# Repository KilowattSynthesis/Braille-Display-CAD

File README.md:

# Braille-Display-CAD

Experimental design for a braille display using build123d CAD in Python

## Interesting Parts

* 4mm x 8mm DC Motors: https://www.aliexpress.com/item/1005004370822475.html
* 2.8mm x 3.9mm DC Motors: https://www.aliexpress.com/item/1005006897190118.html

## Explored Ideas

### Pogo Spools

* Laser printer fuser-like roller mask.
    * Branch: `archive/pogo-spools`
    * Files: `ideas_pogo_spool_mask/`
* Made PCB with small stepper motors, tiny CAD parts (spools).

### RF Inductors as Electromagnets

* Use Mouser's "RF Inductors" selection, mounting an inductor vertically.
    * Branches: `archive/inductor-smd-vertical`, `archive/inductor-smd-flat`
    * Eaton makes good-looking ones. 3225 metric (1210 imp) is too big; 2520 metric (1008 imp) might be okay. 2012 metric (0805 imp) is great!
    * "Power Inductors - Leaded" are never small enough.
    * Filter to >= 20uH inductance. Filter to >=70 mA.
    * Examples (Vertical-Mount):
        * BWLD00241715 -> Not stocked in smaller quantities, though.
            * 2.4 mm x 1.72 mm x 1.52 mm
        * LBR2012T470M -> 0805 imp (2012 metric). 47uH. 75mA rated max.
    * Examples (Horizontal-Mount):
        * VLS201612CX-220M-1 -> 22uF, very good, but shielded.

* Test results:
    * 4mm x 4mm x 3mm 33uH coil-wound SMD power inductor (ASPI-4030S-330M-T) can point a magnet. Magnets stick to the inductor always though.
    * Several inductors, up to 6mm diameter (and 1-2 MH), with 24V get very hot, but don't levitate a 1mm or 2mm neodymium magnet.
        * Good at pointing pointing the magnet, if it starts far away.
        * Cannot remove the magnet from the inductor once it's stuck.

* **Conclusion**: RF inductors don't have enough magnetic force to levitate 1mm or 2mm neodymium magnets.

### Nut/Bolt Grid

* Turn a bolt in a threaded hole/nut. Each bolt is a dot. User directly touches the dot.
* Movement can be done with one motor per dot (very tiny motors, maybe stacked), or motors can be moved between dots (CNC plotter style). Multiple heads can be used.
* Branch: `archive/cnc-plotter`
* Files: `cad/nut_bolt_grid.py`, `cad/vertical_motor_layers.py`

### Silicone Sheet

* Use CNC plotter to manipulate a silicone sheet which can pop up and down.
    * Branch: `archive/silicone-sheet`
    * Files: `cad/silicone_sheet_mold/`

## Unexplored/Unrealized Ideas

* Investigate bi-metallic strip with actuator.
* Investigate shape memory alloy (SMA) approach. Benefit: Would be very quiet.
* Should buy some 4mm solenoids.

* Key and lock mechanism pushes up on the pins

* Use GT2 belt (or similar) to press up on pins.
    * T2.5 belt is probably best - https://www.aliexpress.com/item/1005004668423141.html
    * Could try to TPU 3D print belt with the perfect braille pattern, in a closed loop. Teeth on the inside, and pattern on the outside.
    * Spring pushing on pogo pin flange, on solenoid-relieved cell frame.

* Use CNC plotter to turn pins/bolts for placement. Use hex drive, plus solenoid to mate/un-mate. Build the plotter on a PCB with 3mm linear rails, belts, etc.
    * Branch: `cnc-plotter`
    * Bolt options - Search "M2.5 plunger"
    * Best option: M1.6 Grub Screw, probably.
    * Create top plate with Z-stacked nuts on it.
    * Screw driver or nut will move up and down and turn screws.
    * Search "Micro Linear Motor" for gantry.
    * Focus on M1.6 and M2.5 designs.
    * To move the screw:
        * Use a spring to push the bit up, and a solenoid to pull it down.
        * Use a hex bit maybe, or use rubber friction.
    * BOM:
        * LM3UU linear bearings (ID=3mm, OD=7mm, L=10mm)
        * 3mm Rod x 100mm
        * PM15S Stepper Motors: https://www.aliexpress.com/item/1005005152436475.html
        * GT2 belt
        * GT2 pulley, custom to mate with stepper motor's gear.

* Motors mounted on orthogonal PCBs, with rotating slanted plate to push on the pins.
    * Use magnets as the mating, somehow.

* Microfluidics as valves.

* MEMS on-chip stepper motor:
    * https://www.youtube.com/watch?v=n3YMjgbhvTA
    * Could be useful to drive the screws on the CNC Plotter style.

* Double screw with balls and weird geometry.

* Cams on 2.4mm diameter rods that run along each column of dots.
    * Each cam would have 8 positions, so 45 degrees per position.
    * Would probably need to move table up-and-down independently of the cams.
    * One motor per cam, probably.

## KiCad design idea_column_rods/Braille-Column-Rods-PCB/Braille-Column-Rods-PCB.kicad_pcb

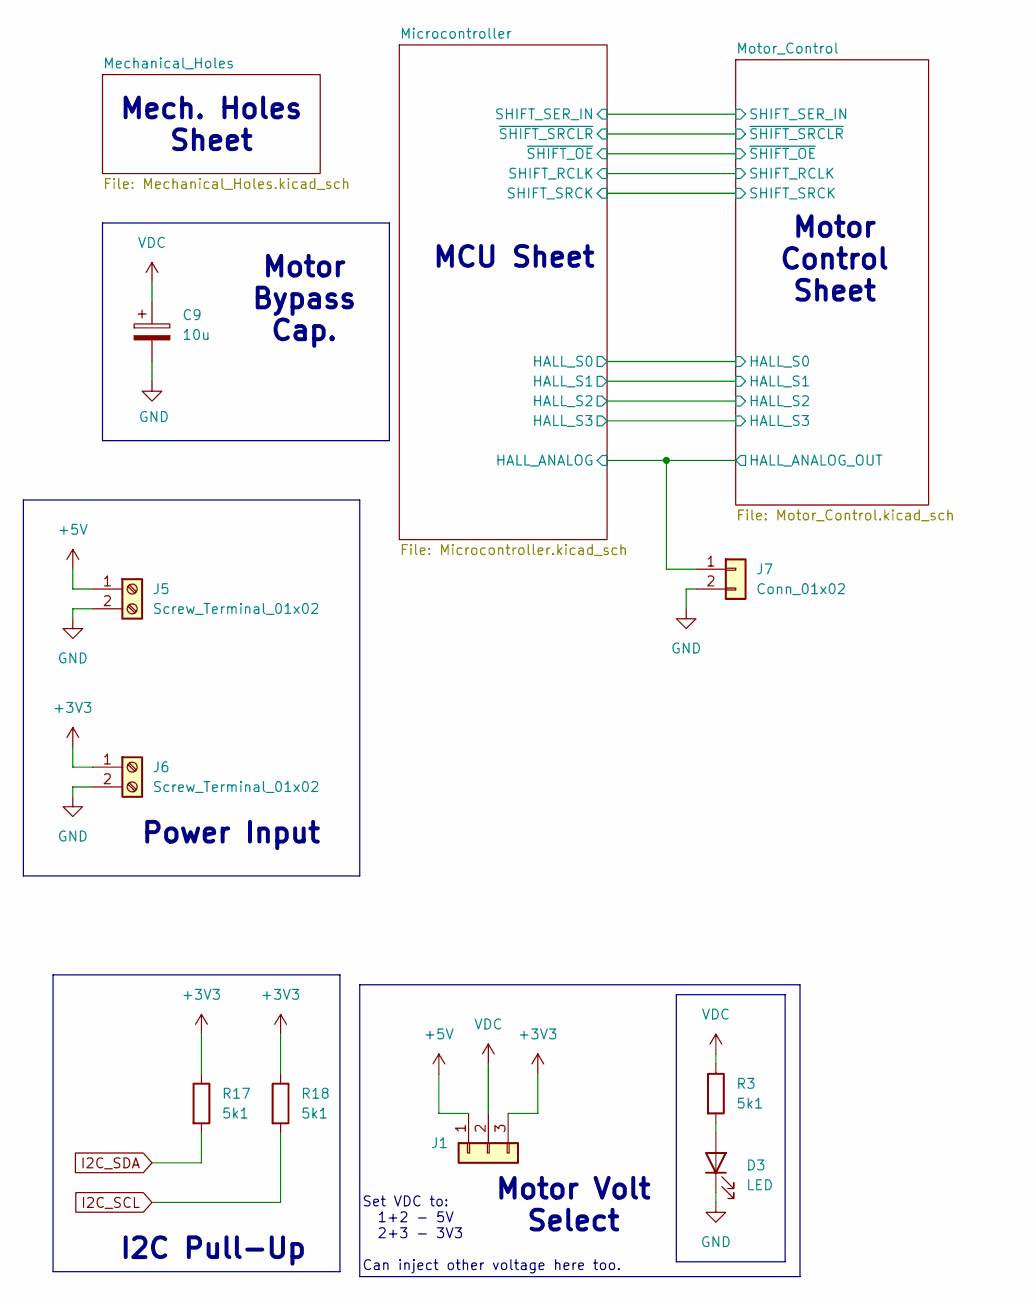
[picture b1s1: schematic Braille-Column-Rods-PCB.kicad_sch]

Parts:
C9: 10u; CP_Radial_D6.3mm_P2.50mm
D3: LED; LED_0603_1608Metric_Pad1.05x0.95mm_HandSolder
J1: Conn_01x03; PinHeader_1x03_P2.54mm_Vertical
J5, J6: Screw_Terminal_01x02; TerminalBlock_bornier-2_P5.08mm
J7: Conn_01x02; PinHeader_1x02_P2.54mm_Vertical
R3, R17, R18: 5k1; R_0603_1608Metric_Pad0.98x0.95mm_HandSolder

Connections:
+3V3: J1.3, J6.1, R17.1, R18.1; also elsewhere on the board
+5V: J1.1, J5.1; also elsewhere on the board
/Microcontroller/HALL_ANALOG: J7.1; also elsewhere on the board
GND: C9.2, D3.1 (K), J5.2, J6.2, J7.2; also elsewhere on the board
I2C_SCL: R18.2; also elsewhere on the board
I2C_SDA: R17.2; also elsewhere on the board
unnamed: D3.2 (A), R3.2
VDC: C9.1, J1.2, R3.1; also elsewhere on the board

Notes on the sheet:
Motor Volt Select
Motor Bypass Cap.
Mech. Holes Sheet
I2C Pull-Up
Set VDC to: 1+2 - 5V 2+3 - 3V3 Can inject other voltage here too.
MCU Sheet
Power Input
Motor Control Sheet

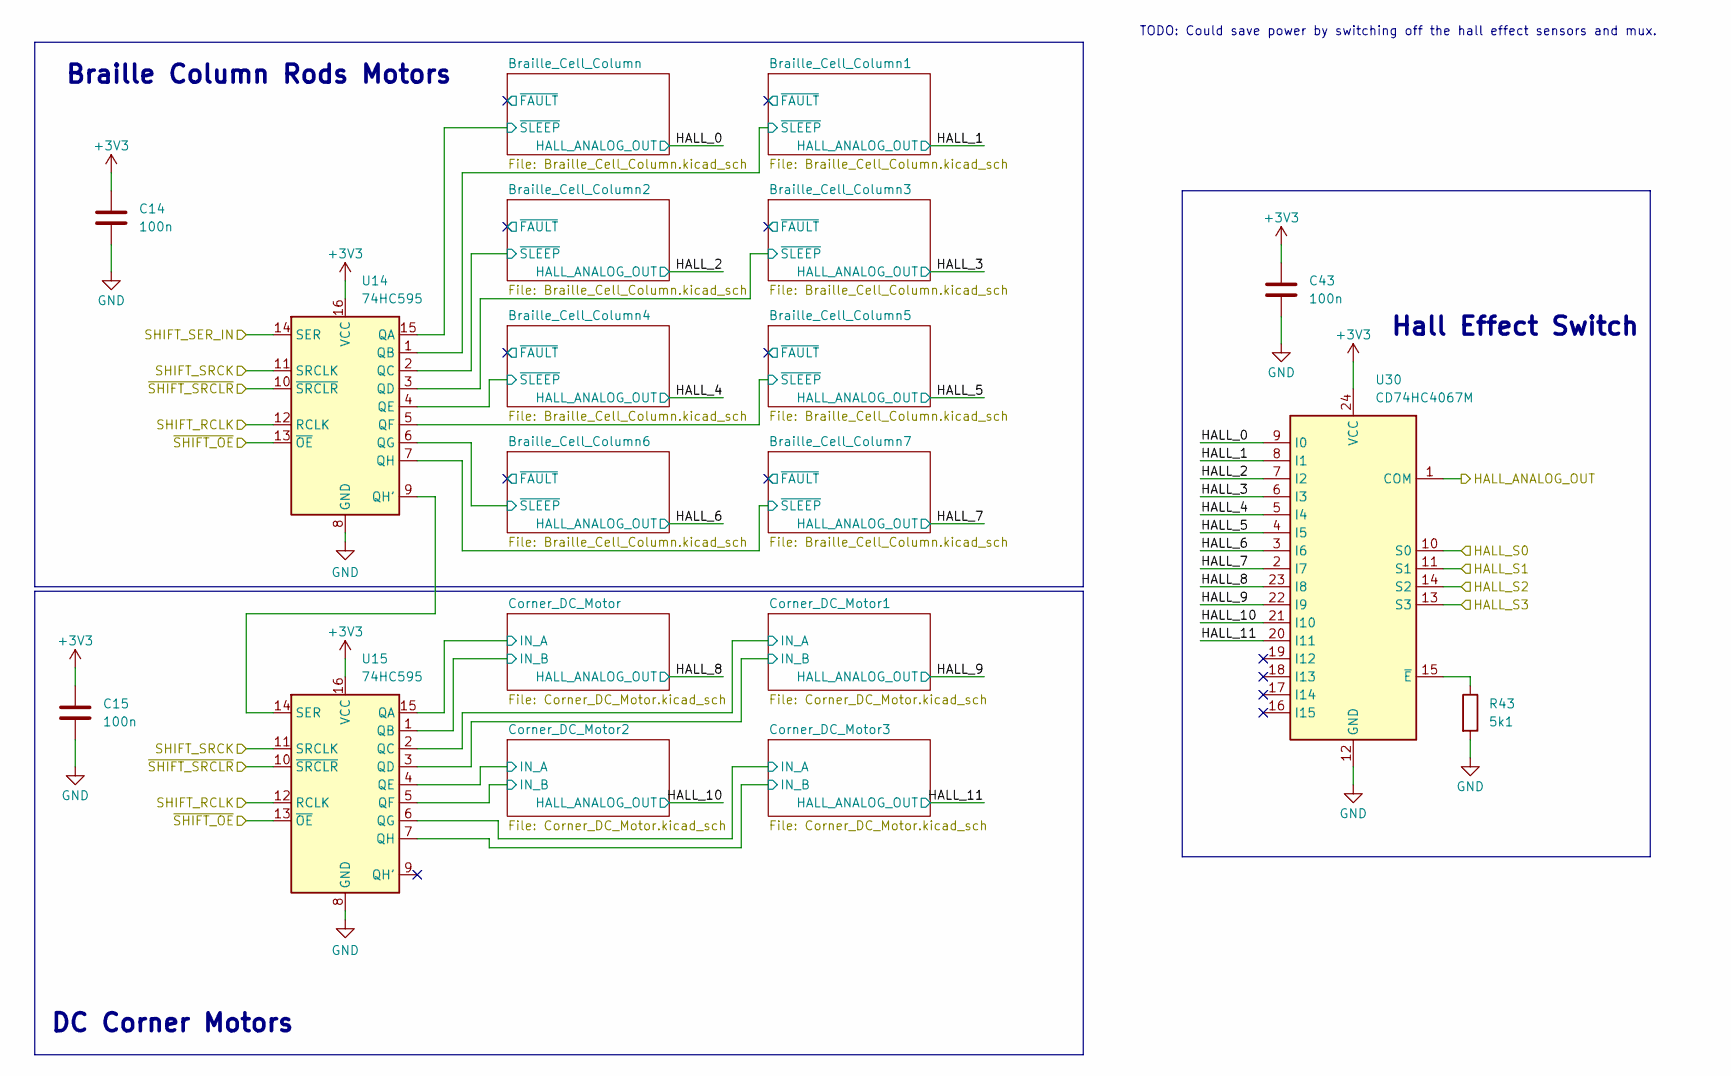
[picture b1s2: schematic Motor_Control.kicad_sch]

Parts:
C14, C15, C43: 100n; C_0603_1608Metric_Pad1.08x0.95mm_HandSolder
R43: 5k1; R_0603_1608Metric_Pad0.98x0.95mm_HandSolder
U14, U15: 74HC595; SOP-16_3.9x9.9mm_P1.27mm
U30: CD74HC4067M; SOIC-24W_7.5x15.4mm_P1.27mm

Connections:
+3V3: C14.1, C15.1, C43.1, U14.16 (VCC), U15.16 (VCC), U30.24 (VCC); also elsewhere on the board
/Microcontroller/HALL_ANALOG: U30.1 (COM); also elsewhere on the board
/Microcontroller/HALL_S0: U30.10 (S0); also elsewhere on the board
/Microcontroller/HALL_S1: U30.11 (S1); also elsewhere on the board
/Microcontroller/HALL_S2: U30.14 (S2); also elsewhere on the board
/Microcontroller/HALL_S3: U30.13 (S3); also elsewhere on the board
/Microcontroller/SHIFT_RCLK: U14.12 (RCLK), U15.12 (RCLK); also elsewhere on the board
/Microcontroller/SHIFT_SER_IN: U14.14 (SER); also elsewhere on the board
/Microcontroller/SHIFT_SRCK: U14.11 (SRCLK), U15.11 (SRCLK); also elsewhere on the board
/Microcontroller/~SHIFT_OE: U14.13 (~OE), U15.13 (~OE); also elsewhere on the board
/Microcontroller/~SHIFT_SRCLR: U14.10 (~SRCLR), U15.10 (~SRCLR); also elsewhere on the board
/Motor_Control/Braille_Cell_Column1/~SLEEP: U14.1 (QB); also elsewhere on the board
/Motor_Control/Braille_Cell_Column2/~SLEEP: U14.2 (QC); also elsewhere on the board
/Motor_Control/Braille_Cell_Column3/~SLEEP: U14.3 (QD); also elsewhere on the board
/Motor_Control/Braille_Cell_Column4/~SLEEP: U14.4 (QE); also elsewhere on the board
/Motor_Control/Braille_Cell_Column5/~SLEEP: U14.5 (QF); also elsewhere on the board
/Motor_Control/Braille_Cell_Column6/~SLEEP: U14.6 (QG); also elsewhere on the board
/Motor_Control/Braille_Cell_Column7/~SLEEP: U14.7 (QH); also elsewhere on the board
/Motor_Control/Braille_Cell_Column/~SLEEP: U14.15 (QA); also elsewhere on the board
/Motor_Control/Corner_DC_Motor1/IN_A: U15.2 (QC); also elsewhere on the board
/Motor_Control/Corner_DC_Motor1/IN_B: U15.3 (QD); also elsewhere on the board
/Motor_Control/Corner_DC_Motor2/IN_A: U15.4 (QE); also elsewhere on the board
/Motor_Control/Corner_DC_Motor2/IN_B: U15.5 (QF); also elsewhere on the board
/Motor_Control/Corner_DC_Motor3/IN_A: U15.6 (QG); also elsewhere on the board
/Motor_Control/Corner_DC_Motor3/IN_B: U15.7 (QH); also elsewhere on the board
/Motor_Control/Corner_DC_Motor/IN_A: U15.15 (QA); also elsewhere on the board
/Motor_Control/Corner_DC_Motor/IN_B: U15.1 (QB); also elsewhere on the board
/Motor_Control/HALL_0: U30.9 (I0); also elsewhere on the board
/Motor_Control/HALL_1: U30.8 (I1); also elsewhere on the board
/Motor_Control/HALL_2: U30.7 (I2); also elsewhere on the board
/Motor_Control/HALL_3: U30.6 (I3); also elsewhere on the board
/Motor_Control/HALL_4: U30.5 (I4); also elsewhere on the board
/Motor_Control/HALL_5: U30.4 (I5); also elsewhere on the board
/Motor_Control/HALL_6: U30.3 (I6); also elsewhere on the board
/Motor_Control/HALL_7: U30.2 (I7); also elsewhere on the board
/Motor_Control/HALL_8: U30.23 (I8); also elsewhere on the board
/Motor_Control/HALL_9: U30.22 (I9); also elsewhere on the board
/Motor_Control/HALL_10: U30.21 (I10); also elsewhere on the board
/Motor_Control/HALL_11: U30.20 (I11); also elsewhere on the board
GND: C14.2, C15.2, C43.2, R43.2, U14.8 (GND), U15.8 (GND), U30.12 (GND); also elsewhere on the board
unnamed: U14.9 (QH'), U15.14 (SER)
unnamed: R43.1, U30.15 (~E)

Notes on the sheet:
Hall Effect Switch
Braille Column Rods Motors
TODO: Could save power by switching off the hall effect sensors and mux.
DC Corner Motors

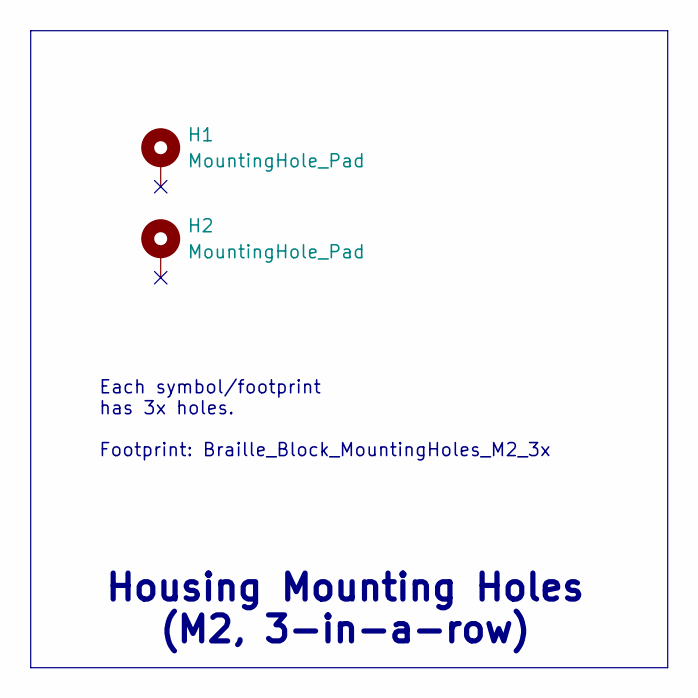
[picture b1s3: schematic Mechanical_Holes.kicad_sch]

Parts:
H1, H2: MountingHole_Pad; Braille_Block_MountingHoles_M2_3x

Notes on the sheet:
Each symbol/footprint has 3x holes. Footprint: Braille_Block_MountingHoles_M2_3x
Housing Mounting Holes (M2, 3-in-a-row)

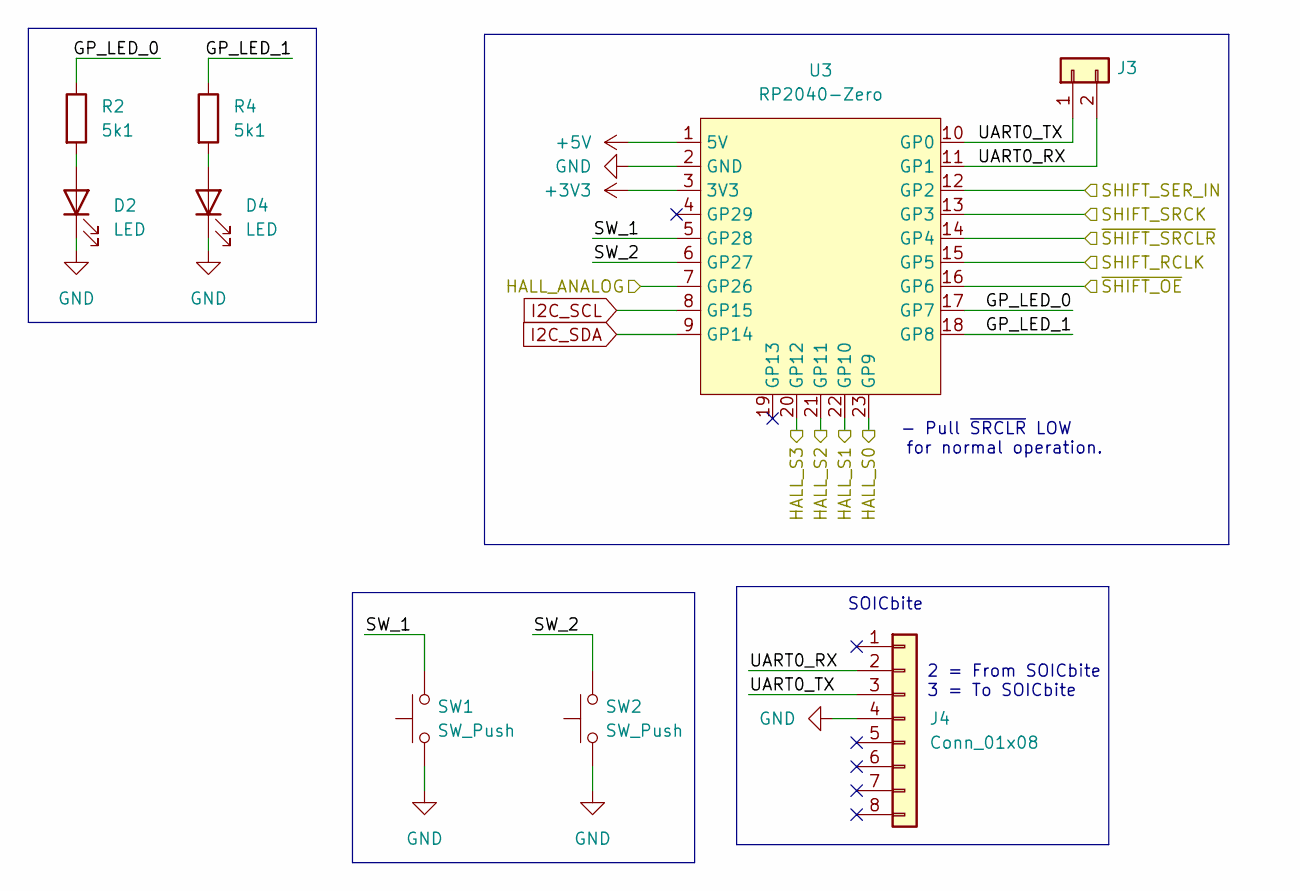
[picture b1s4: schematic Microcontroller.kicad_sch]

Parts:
D2, D4: LED; LED_0603_1608Metric_Pad1.05x0.95mm_HandSolder
J3: Conn_01x02; PinHeader_1x02_P2.54mm_Vertical
J4: Conn_01x08; SOICbite_clipProgSmall
R2, R4: 5k1; R_0603_1608Metric_Pad0.98x0.95mm_HandSolder
SW1, SW2: SW_Push; PushButtonSMD_2.93x3.9
U3: RP2040-Zero; RP2040 Zero

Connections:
+3V3: U3.3 (3V3); also elsewhere on the board
+5V: U3.1 (5V); also elsewhere on the board
/Microcontroller/GP_LED_0: R2.1, U3.17 (GP7)
/Microcontroller/GP_LED_1: R4.1, U3.18 (GP8)
/Microcontroller/HALL_ANALOG: U3.7 (GP26); also elsewhere on the board
/Microcontroller/HALL_S0: U3.23 (GP9); also elsewhere on the board
/Microcontroller/HALL_S1: U3.22 (GP10); also elsewhere on the board
/Microcontroller/HALL_S2: U3.21 (GP11); also elsewhere on the board
/Microcontroller/HALL_S3: U3.20 (GP12); also elsewhere on the board
/Microcontroller/SHIFT_RCLK: U3.15 (GP5); also elsewhere on the board
/Microcontroller/SHIFT_SER_IN: U3.12 (GP2); also elsewhere on the board
/Microcontroller/SHIFT_SRCK: U3.13 (GP3); also elsewhere on the board
/Microcontroller/SW_1: SW1.2, U3.5 (GP28)
/Microcontroller/SW_2: SW2.2, U3.6 (GP27)
/Microcontroller/UART0_RX: J3.2, J4.2, U3.11 (GP1)
/Microcontroller/UART0_TX: J3.1, J4.3, U3.10 (GP0)
/Microcontroller/~SHIFT_OE: U3.16 (GP6); also elsewhere on the board
/Microcontroller/~SHIFT_SRCLR: U3.14 (GP4); also elsewhere on the board
GND: D2.1 (K), D4.1 (K), J4.4, SW1.1, SW2.1, U3.2 (GND); also elsewhere on the board
I2C_SCL: U3.8 (GP15); also elsewhere on the board
I2C_SDA: U3.9 (GP14); also elsewhere on the board
unnamed: D2.2 (A), R2.2
unnamed: D4.2 (A), R4.2

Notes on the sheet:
SOICbite
2 = From SOICbite 3 = To SOICbite
- Pull ~{SRCLR} LOW for normal operation.

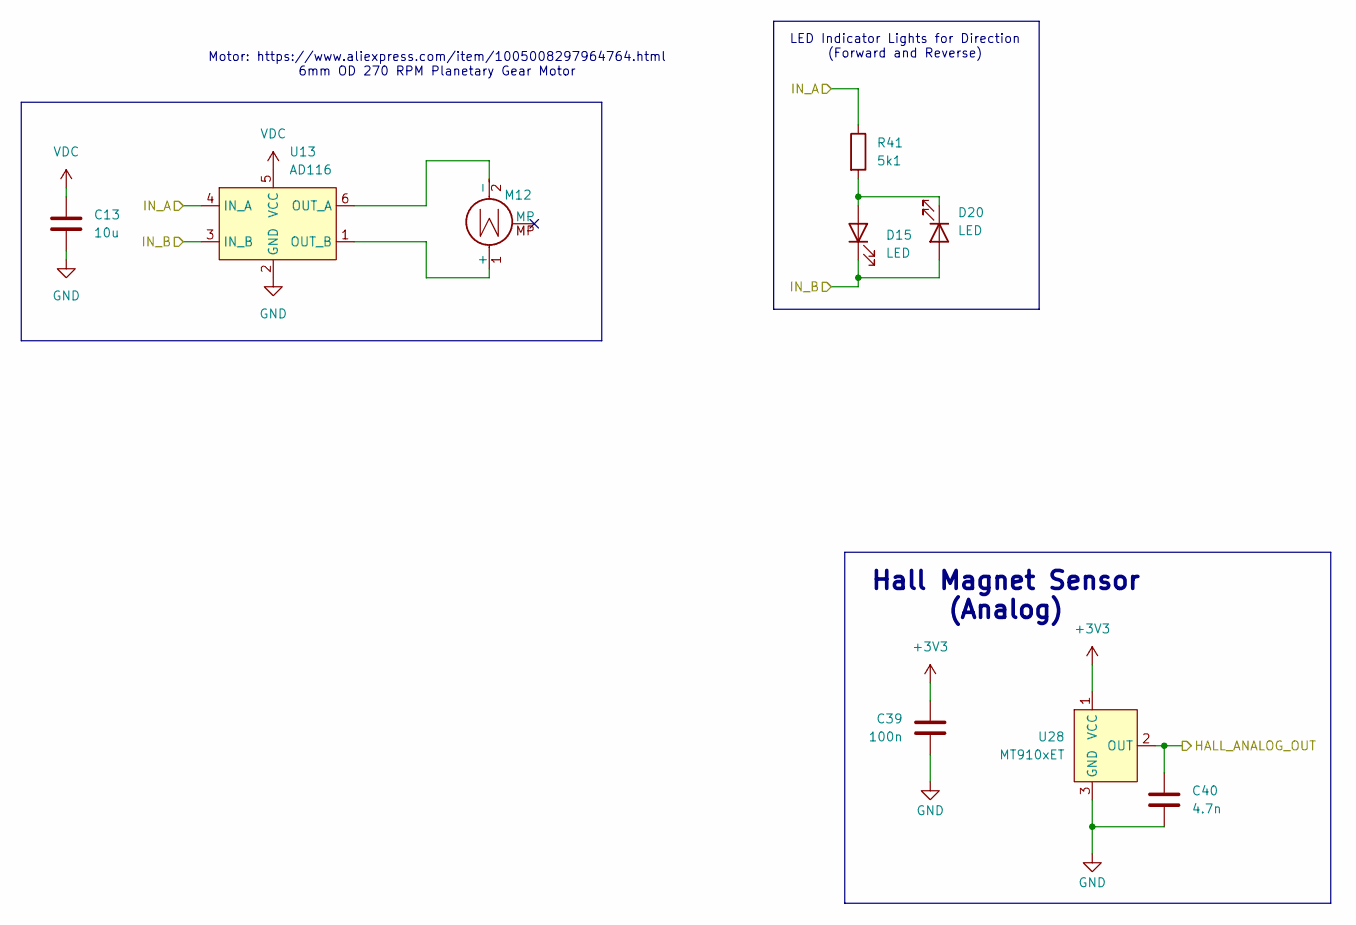
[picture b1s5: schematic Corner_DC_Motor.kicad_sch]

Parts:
C13: 10u; C_1206_3216Metric_Pad1.33x1.80mm_HandSolder
C39: 100n; C_0603_1608Metric_Pad1.08x0.95mm_HandSolder
C40: 4.7n; C_0603_1608Metric_Pad1.08x0.95mm_HandSolder
D15, D20: LED; LED_0603_1608Metric_Pad1.05x0.95mm_HandSolder
M12: Motor_DC_With_MP; DC_Motor_6mm_OD_with_3_Stage_Gearbox
R41: 5k1; R_0603_1608Metric_Pad0.98x0.95mm_HandSolder
U13: AD116; SOT-23-6
U28: MT910xET; SOT-23-Hall

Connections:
+3V3: C39.1, U28.1 (VCC); also elsewhere on the board
/Motor_Control/Corner_DC_Motor3/IN_A: R41.1, U13.4 (IN_A); also elsewhere on the board
/Motor_Control/Corner_DC_Motor3/IN_B: D15.1 (K), D20.2 (A), U13.3 (IN_B); also elsewhere on the board
/Motor_Control/HALL_11: C40.1, U28.2 (OUT); also elsewhere on the board
GND: C13.2, C39.2, C40.2, U13.2 (GND), U28.3 (GND); also elsewhere on the board
unnamed: D15.2 (A), D20.1 (K), R41.2
unnamed: M12.1 (+), U13.1 (OUT_B)
unnamed: M12.2 (-), U13.6 (OUT_A)
VDC: C13.1, U13.5 (VCC); also elsewhere on the board

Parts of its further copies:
C10, C11, C12: 10u; C_1206_3216Metric_Pad1.33x1.80mm_HandSolder
C33, C35, C37: 100n; C_0603_1608Metric_Pad1.08x0.95mm_HandSolder
C34, C36, C38: 4.7n; C_0603_1608Metric_Pad1.08x0.95mm_HandSolder
D12, D13, D14, D17, D18, D19: LED; LED_0603_1608Metric_Pad1.05x0.95mm_HandSolder
M9, M10, M11: Motor_DC_With_MP; DC_Motor_6mm_OD_with_3_Stage_Gearbox
R38, R39, R40: 5k1; R_0603_1608Metric_Pad0.98x0.95mm_HandSolder
U10, U11, U12: AD116; SOT-23-6
U25, U26, U27: MT910xET; SOT-23-Hall

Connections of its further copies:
+3V3: C33.1, C35.1, C37.1, U25.1 (VCC), U26.1 (VCC), U27.1 (VCC); also elsewhere on the board
/Motor_Control/Corner_DC_Motor1/IN_A: R39.1, U11.4 (IN_A); also elsewhere on the board
/Motor_Control/Corner_DC_Motor1/IN_B: D13.1 (K), D18.2 (A), U11.3 (IN_B); also elsewhere on the board
/Motor_Control/Corner_DC_Motor2/IN_A: R40.1, U12.4 (IN_A); also elsewhere on the board
/Motor_Control/Corner_DC_Motor2/IN_B: D14.1 (K), D19.2 (A), U12.3 (IN_B); also elsewhere on the board
/Motor_Control/Corner_DC_Motor/IN_A: R38.1, U10.4 (IN_A); also elsewhere on the board
/Motor_Control/Corner_DC_Motor/IN_B: D12.1 (K), D17.2 (A), U10.3 (IN_B); also elsewhere on the board
/Motor_Control/HALL_8: C34.1, U25.2 (OUT); also elsewhere on the board
/Motor_Control/HALL_9: C36.1, U26.2 (OUT); also elsewhere on the board
/Motor_Control/HALL_10: C38.1, U27.2 (OUT); also elsewhere on the board
GND: C10.2, C11.2, C12.2, C33.2, C34.2, C35.2, C36.2, C37.2, C38.2, U10.2 (GND), U11.2 (GND), U12.2 (GND), U25.3 (GND), U26.3 (GND), U27.3 (GND); also elsewhere on the board
unnamed: D12.2 (A), D17.1 (K), R38.2
unnamed: D13.2 (A), D18.1 (K), R39.2
unnamed: D14.2 (A), D19.1 (K), R40.2
unnamed: M9.1 (+), U10.1 (OUT_B)
unnamed: M9.2 (-), U10.6 (OUT_A)
unnamed: M10.1 (+), U11.1 (OUT_B)
unnamed: M10.2 (-), U11.6 (OUT_A)
unnamed: M11.1 (+), U12.1 (OUT_B)
unnamed: M11.2 (-), U12.6 (OUT_A)
VDC: C10.1, C11.1, C12.1, U10.5 (VCC), U11.5 (VCC), U12.5 (VCC); also elsewhere on the board

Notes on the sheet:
LED Indicator Lights for Direction (Forward and Reverse)
Hall Magnet Sensor (Analog)
Motor: https://www.aliexpress.com/item/1005008297964764.html 6mm OD 270 RPM Planetary Gear Motor

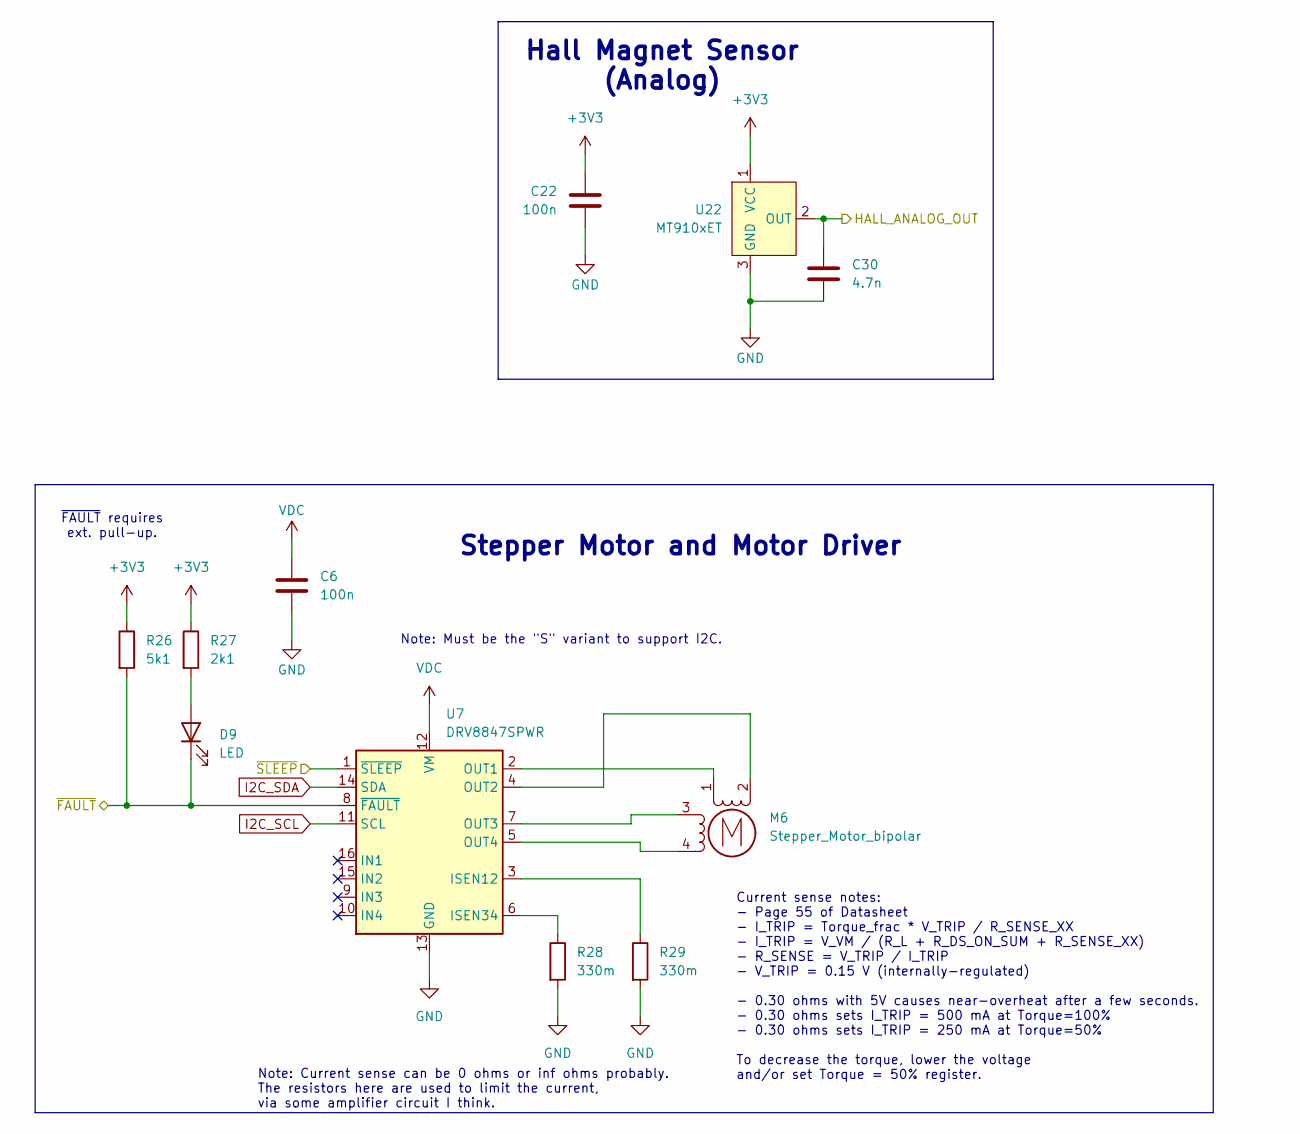
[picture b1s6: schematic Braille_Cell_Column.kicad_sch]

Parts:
C6, C22: 100n; C_0603_1608Metric_Pad1.08x0.95mm_HandSolder
C30: 4.7n; C_0603_1608Metric_Pad1.08x0.95mm_HandSolder
D9: LED; LED_0603_1608Metric_Pad1.05x0.95mm_HandSolder
M6: Stepper_Motor_bipolar; MicroStepper_4.7_OD
R26: 5k1; R_0603_1608Metric_Pad0.98x0.95mm_HandSolder
R27: 2k1; R_0603_1608Metric_Pad0.98x0.95mm_HandSolder
R28, R29: 330m; R_0603_1608Metric_Pad0.98x0.95mm_HandSolder
U7: DRV8847SPWR; TSSOP-16_4.4x5mm_P0.65mm
U22: MT910xET; SOT-23-Hall

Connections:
+3V3: C22.1, R26.1, R27.1, U22.1 (VCC); also elsewhere on the board
/Motor_Control/Braille_Cell_Column5/~FAULT: D9.1 (K), R26.2, U7.8 (~FAULT)
/Motor_Control/Braille_Cell_Column5/~SLEEP: U7.1 (~SLEEP); also elsewhere on the board
/Motor_Control/HALL_5: C30.1, U22.2 (OUT); also elsewhere on the board
GND: C6.2, C22.2, C30.2, R28.2, R29.2, U7.13 (GND), U22.3 (GND); also elsewhere on the board
I2C_SCL: U7.11 (SCL); also elsewhere on the board
I2C_SDA: U7.14 (SDA); also elsewhere on the board
unnamed: D9.2 (A), R27.2
unnamed: M6.2 (-), U7.4 (OUT2)
unnamed: R29.1, U7.3 (ISEN12)
unnamed: R28.1, U7.6 (ISEN34)
unnamed: M6.1, U7.2 (OUT1)
unnamed: M6.3, U7.7 (OUT3)
unnamed: M6.4, U7.5 (OUT4)
VDC: C6.1, U7.12 (VM); also elsewhere on the board

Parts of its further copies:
C1, C2, C3, C4, C5, C7, C8, C17, C18, C19, C20, C21, C23, C24: 100n; C_0603_1608Metric_Pad1.08x0.95mm_HandSolder
C25, C26, C27, C28, C29, C31, C32: 4.7n; C_0603_1608Metric_Pad1.08x0.95mm_HandSolder
D1, D5, D6, D7, D8, D10, D11: LED; LED_0603_1608Metric_Pad1.05x0.95mm_HandSolder
M1, M2, M3, M4, M5, M7, M8: Stepper_Motor_bipolar; MicroStepper_4.7_OD
R1, R8, R12, R16, R22, R30, R34: 5k1; R_0603_1608Metric_Pad0.98x0.95mm_HandSolder
R5, R9, R13, R19, R23, R31, R35: 2k1; R_0603_1608Metric_Pad0.98x0.95mm_HandSolder
R6, R7, R10, R11, R14, R15, R20, R21, R24, R25, R32, R33, R36, R37: 330m; R_0603_1608Metric_Pad0.98x0.95mm_HandSolder
U1, U2, U4, U5, U6, U8, U9: DRV8847SPWR; TSSOP-16_4.4x5mm_P0.65mm
U17, U18, U19, U20, U21, U23, U24: MT910xET; SOT-23-Hall

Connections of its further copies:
+3V3: C17.1, C18.1, C19.1, C20.1, C21.1, C23.1, C24.1, R1.1, R5.1, R8.1, R9.1, R12.1, R13.1, R16.1, R19.1, R22.1, R23.1, R30.1, R31.1, R34.1, R35.1, U17.1 (VCC), U18.1 (VCC), U19.1 (VCC), U20.1 (VCC), U21.1 (VCC), U23.1 (VCC), U24.1 (VCC); also elsewhere on the board
/Motor_Control/Braille_Cell_Column1/~FAULT: D5.1 (K), R8.2, U2.8 (~FAULT)
/Motor_Control/Braille_Cell_Column1/~SLEEP: U2.1 (~SLEEP); also elsewhere on the board
/Motor_Control/Braille_Cell_Column2/~FAULT: D6.1 (K), R12.2, U4.8 (~FAULT)
/Motor_Control/Braille_Cell_Column2/~SLEEP: U4.1 (~SLEEP); also elsewhere on the board
/Motor_Control/Braille_Cell_Column3/~FAULT: D7.1 (K), R16.2, U5.8 (~FAULT)
/Motor_Control/Braille_Cell_Column3/~SLEEP: U5.1 (~SLEEP); also elsewhere on the board
/Motor_Control/Braille_Cell_Column4/~FAULT: D8.1 (K), R22.2, U6.8 (~FAULT)
/Motor_Control/Braille_Cell_Column4/~SLEEP: U6.1 (~SLEEP); also elsewhere on the board
/Motor_Control/Braille_Cell_Column6/~FAULT: D10.1 (K), R30.2, U8.8 (~FAULT)
/Motor_Control/Braille_Cell_Column6/~SLEEP: U8.1 (~SLEEP); also elsewhere on the board
/Motor_Control/Braille_Cell_Column7/~FAULT: D11.1 (K), R34.2, U9.8 (~FAULT)
/Motor_Control/Braille_Cell_Column7/~SLEEP: U9.1 (~SLEEP); also elsewhere on the board
/Motor_Control/Braille_Cell_Column/~FAULT: D1.1 (K), R1.2, U1.8 (~FAULT)
/Motor_Control/Braille_Cell_Column/~SLEEP: U1.1 (~SLEEP); also elsewhere on the board
/Motor_Control/HALL_0: C25.1, U17.2 (OUT); also elsewhere on the board
/Motor_Control/HALL_1: C26.1, U18.2 (OUT); also elsewhere on the board
/Motor_Control/HALL_2: C27.1, U19.2 (OUT); also elsewhere on the board
/Motor_Control/HALL_3: C28.1, U20.2 (OUT); also elsewhere on the board
/Motor_Control/HALL_4: C29.1, U21.2 (OUT); also elsewhere on the board
/Motor_Control/HALL_6: C31.1, U23.2 (OUT); also elsewhere on the board
/Motor_Control/HALL_7: C32.1, U24.2 (OUT); also elsewhere on the board
GND: C1.2, C2.2, C3.2, C4.2, C5.2, C7.2, C8.2, C17.2, C18.2, C19.2, C20.2, C21.2, C23.2, C24.2, C25.2, C26.2, C27.2, C28.2, C29.2, C31.2, C32.2, R6.2, R7.2, R10.2, R11.2, R14.2, R15.2, R20.2, R21.2, R24.2, R25.2, R32.2, R33.2, R36.2, R37.2, U1.13 (GND), U2.13 (GND), U4.13 (GND), U5.13 (GND), U6.13 (GND), U8.13 (GND), U9.13 (GND), U17.3 (GND), U18.3 (GND), U19.3 (GND), U20.3 (GND), U21.3 (GND), U23.3 (GND), U24.3 (GND); also elsewhere on the board
I2C_SCL: U1.11 (SCL), U2.11 (SCL), U4.11 (SCL), U5.11 (SCL), U6.11 (SCL), U8.11 (SCL), U9.11 (SCL); also elsewhere on the board
I2C_SDA: U1.14 (SDA), U2.14 (SDA), U4.14 (SDA), U5.14 (SDA), U6.14 (SDA), U8.14 (SDA), U9.14 (SDA); also elsewhere on the board
unnamed: D1.2 (A), R5.2
unnamed: D5.2 (A), R9.2
unnamed: D6.2 (A), R13.2
unnamed: D7.2 (A), R19.2
unnamed: D8.2 (A), R23.2
unnamed: D10.2 (A), R31.2
unnamed: D11.2 (A), R35.2
unnamed: M1.2 (-), U1.4 (OUT2)
unnamed: M2.2 (-), U2.4 (OUT2)
unnamed: M3.2 (-), U4.4 (OUT2)
unnamed: M4.2 (-), U5.4 (OUT2)
unnamed: M5.2 (-), U6.4 (OUT2)
unnamed: M7.2 (-), U8.4 (OUT2)
unnamed: M8.2 (-), U9.4 (OUT2)
unnamed: R7.1, U1.3 (ISEN12)
unnamed: R6.1, U1.6 (ISEN34)
unnamed: M1.1, U1.2 (OUT1)
unnamed: M1.3, U1.7 (OUT3)
unnamed: M1.4, U1.5 (OUT4)
unnamed: R11.1, U2.3 (ISEN12)
unnamed: R10.1, U2.6 (ISEN34)
unnamed: M2.1, U2.2 (OUT1)
unnamed: M2.3, U2.7 (OUT3)
unnamed: M2.4, U2.5 (OUT4)
unnamed: R15.1, U4.3 (ISEN12)
unnamed: R14.1, U4.6 (ISEN34)
unnamed: M3.1, U4.2 (OUT1)
unnamed: M3.3, U4.7 (OUT3)
unnamed: M3.4, U4.5 (OUT4)
unnamed: R21.1, U5.3 (ISEN12)
unnamed: R20.1, U5.6 (ISEN34)
unnamed: M4.1, U5.2 (OUT1)
unnamed: M4.3, U5.7 (OUT3)
unnamed: M4.4, U5.5 (OUT4)
unnamed: R25.1, U6.3 (ISEN12)
unnamed: R24.1, U6.6 (ISEN34)
unnamed: M5.1, U6.2 (OUT1)
unnamed: M5.3, U6.7 (OUT3)
unnamed: M5.4, U6.5 (OUT4)
unnamed: R33.1, U8.3 (ISEN12)
unnamed: R32.1, U8.6 (ISEN34)
unnamed: M7.1, U8.2 (OUT1)
unnamed: M7.3, U8.7 (OUT3)
unnamed: M7.4, U8.5 (OUT4)
unnamed: R37.1, U9.3 (ISEN12)
unnamed: R36.1, U9.6 (ISEN34)
unnamed: M8.1, U9.2 (OUT1)
unnamed: M8.3, U9.7 (OUT3)
unnamed: M8.4, U9.5 (OUT4)
VDC: C1.1, C2.1, C3.1, C4.1, C5.1, C7.1, C8.1, U1.12 (VM), U2.12 (VM), U4.12 (VM), U5.12 (VM), U6.12 (VM), U8.12 (VM), U9.12 (VM); also elsewhere on the board

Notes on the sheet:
Note: Current sense can be 0 ohms or inf ohms probably. The resistors here are used to limit the current, via some amplifier circuit I think.
Current sense notes: - Page 55 of Datasheet - I_TRIP = Torque_frac * V_TRIP / R_SENSE_XX - I_TRIP = V_VM / (R_L + R_DS_ON_SUM + R_SENSE_XX) - R_SENSE = V_TRIP / I_TRIP - V_TRIP = 0.15 V (internally-regulated) - 0.30 ohms with 5V causes near-overheat after a few seconds. - 0.30 ohms sets I_TRIP = 50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
~{FAULT} requires ext. pull-up.
Note: Must be the "S" variant to support I2C.
Stepper Motor and Motor Driver
Hall Magnet Sensor (Analog)

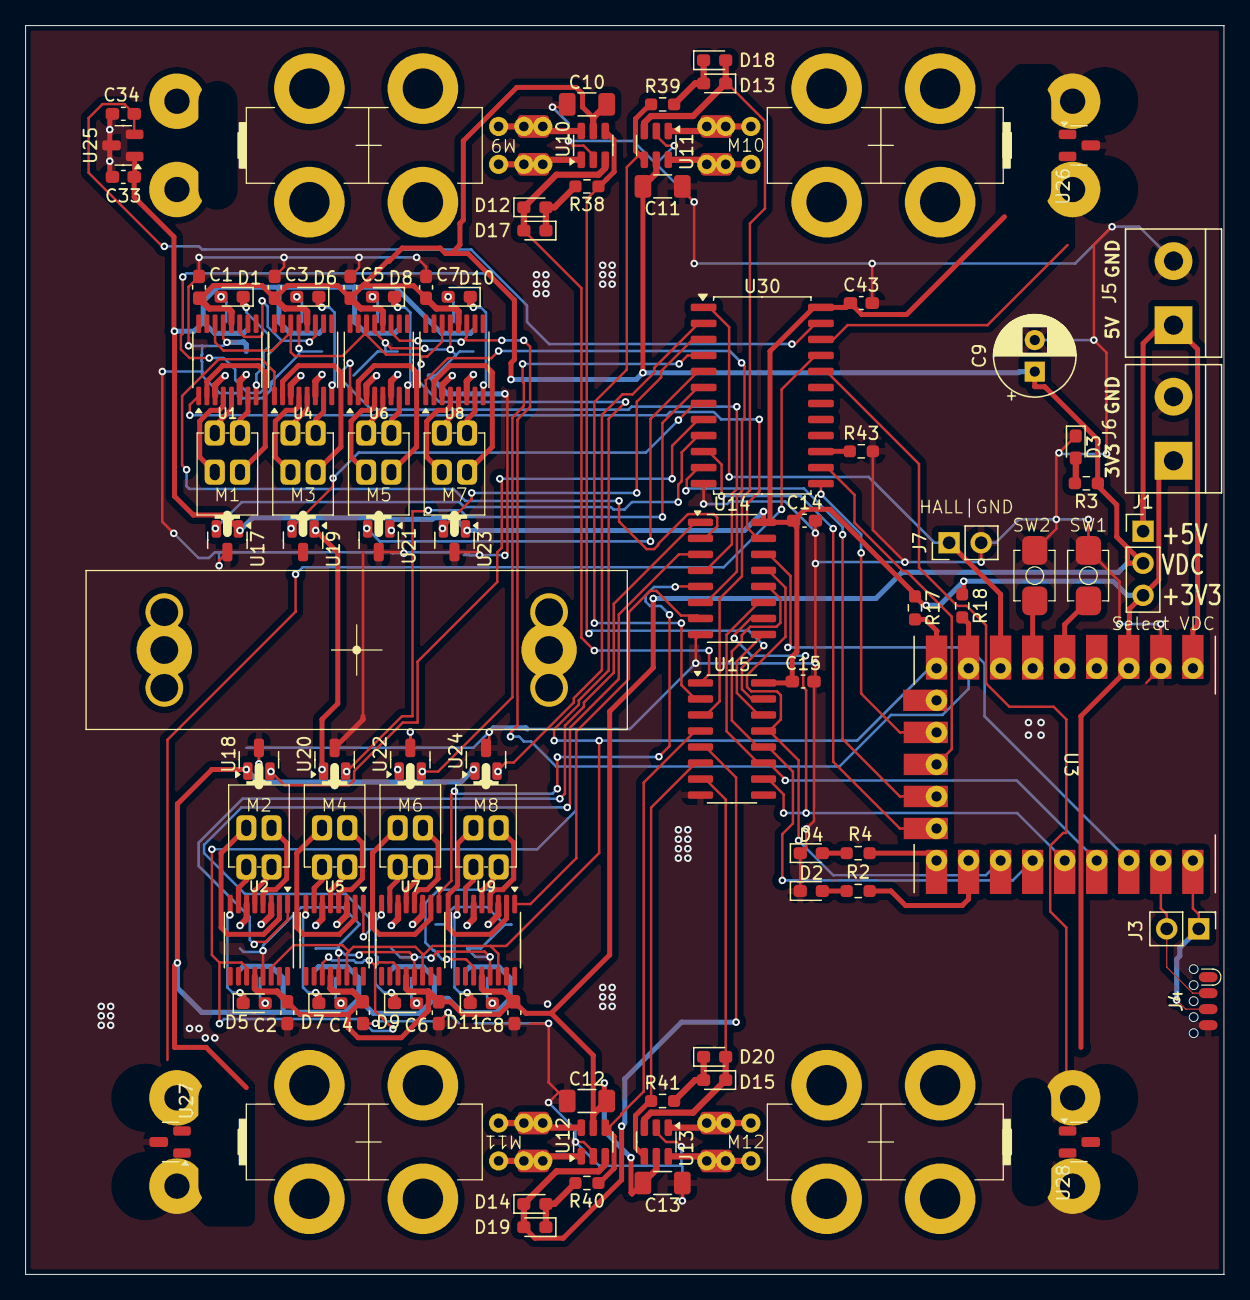
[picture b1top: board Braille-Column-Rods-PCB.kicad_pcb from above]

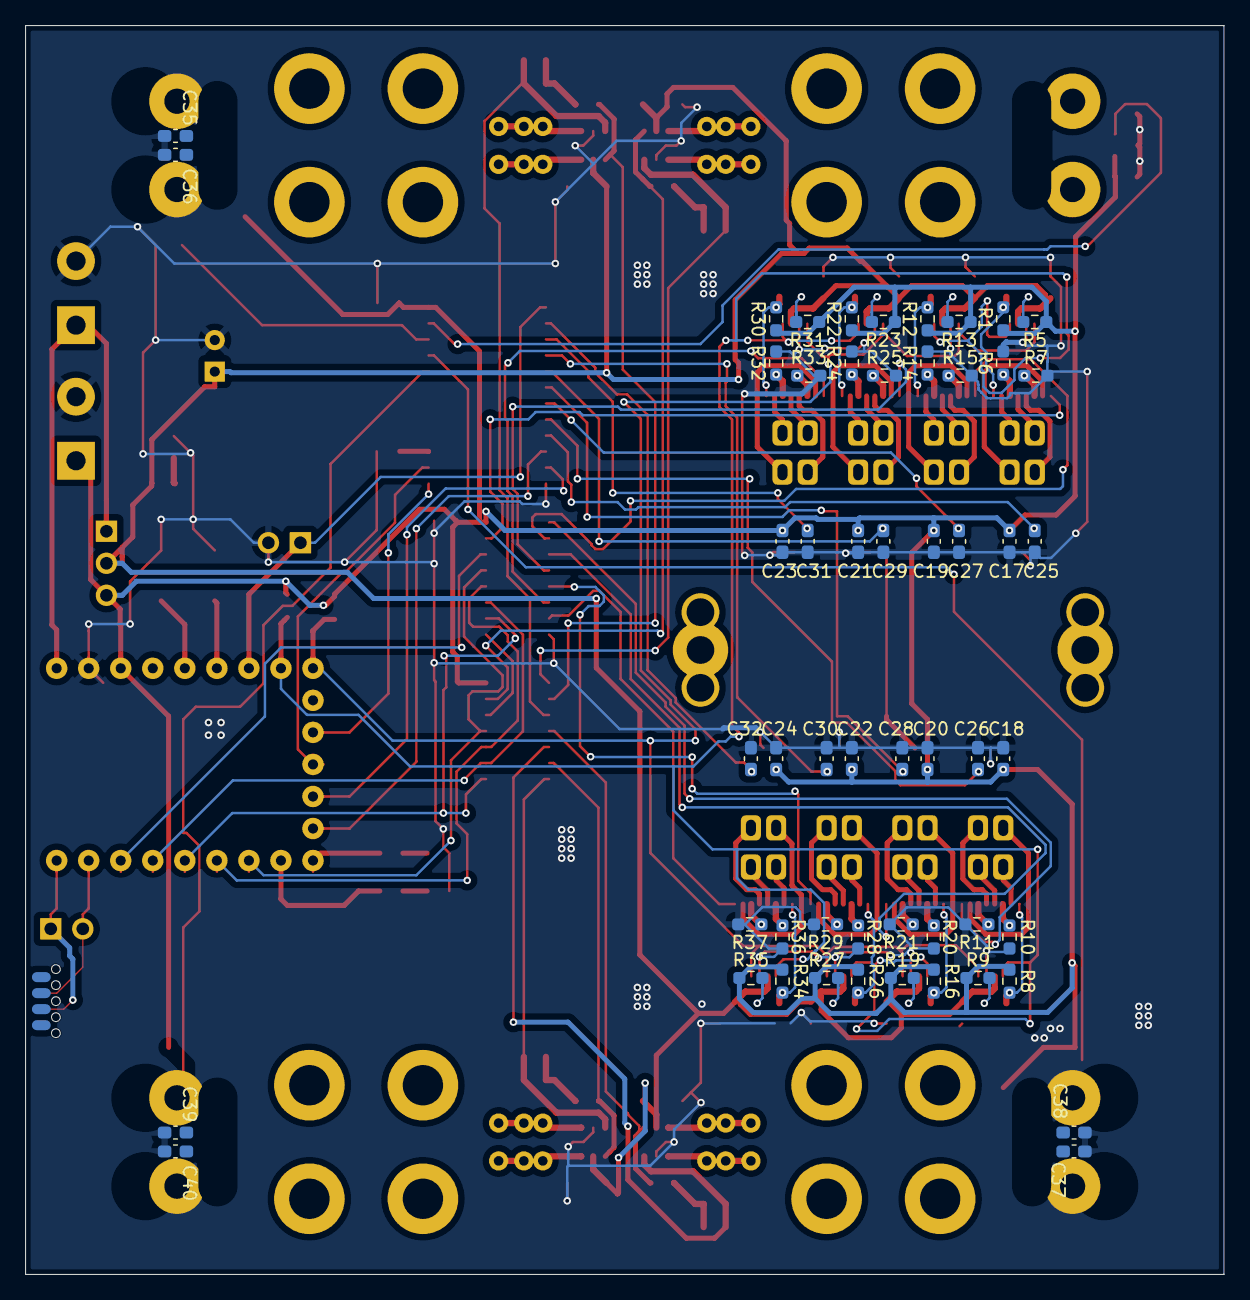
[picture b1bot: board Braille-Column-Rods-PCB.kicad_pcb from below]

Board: 2 copper layers, 95.0 x 99.0 mm, 151 parts (54 on the bottom side), 131 nets.
